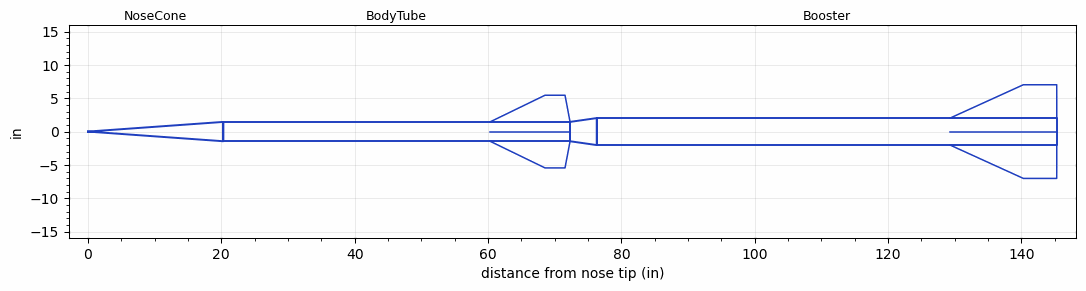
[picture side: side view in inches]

<RASAeroDocument>
 <FileVersion>2</FileVersion>
 <RocketDesign>
  <NoseCone>
   <Length>20.3</Length>
   <Diameter>2.9</Diameter>
   <Shape>Conical</Shape>
   <BluntRadius>0.02</BluntRadius>
   <Location>0</Location>
  </NoseCone>
  <BodyTube>
   <Length>51.9999</Length>
   <Diameter>2.9</Diameter>
   <Location>20.3</Location>
   <Fin>
    <Count>4</Count>
    <Chord>12</Chord>
    <Span>4</Span>
    <SweepDistance>8.2424</SweepDistance>
    <TipChord>3</TipChord>
    <Thickness>0.1875</Thickness>
    <LERadius>0.02</LERadius>
    <Location>12</Location>
    <AirfoilSection>Hexagonal</AirfoilSection>
    <FX1>1</FX1>
    <FX3>1</FX3>
   </Fin>
  </BodyTube>
  <Booster>
   <Length>68.9999</Length>
   <Diameter>4.05</Diameter>
   <InsideDiameter>2.9</InsideDiameter>
   <Location>72.2999</Location>
   <ShoulderLength>4</ShoulderLength>
   <Fin>
    <Count>4</Count>
    <Chord>16</Chord>
    <Span>5</Span>
    <SweepDistance>10.9899</SweepDistance>
    <TipChord>5</TipChord>
    <Thickness>0.25</Thickness>
    <LERadius>0.02</LERadius>
    <Location>16</Location>
    <AirfoilSection>Hexagonal</AirfoilSection>
    <FX1>1</FX1>
    <FX3>1</FX3>
   </Fin>
  </Booster>
  <Surface>Rough Camouflage Paint</Surface>
  <ModifiedBarrowman>False</ModifiedBarrowman>
  <Turbulence>False</Turbulence>
  <UseBooster1>True</UseBooster1>
  <UseBooster2>False</UseBooster2>
 </RocketDesign>
 <LaunchSite>
  <Altitude>0</Altitude>
  <Pressure>29.9214</Pressure>
  <RodAngle>0</RodAngle>
  <RodLength>71.9999</RodLength>
  <Temperature>59</Temperature>
  <WindSpeed>4.4739</WindSpeed>
 </LaunchSite>
 <Recovery>
  <Altitude1>0</Altitude1>
  <Altitude2>0</Altitude2>
  <DeviceType1>None</DeviceType1>
  <DeviceType2>None</DeviceType2>
  <Event1>False</Event1>
  <Event2>False</Event2>
  <Size1>0</Size1>
  <Size2>0</Size2>
  <EventType1>None</EventType1>
  <EventType2>None</EventType2>
  <CD1>0</CD1>
  <CD2>0</CD2>
 </Recovery>
 <SimulationList>
  <Simulation>
   <SustainerEngine>N3650FB  (Polaris)</SustainerEngine>
   <SustainerLaunchWt>20</SustainerLaunchWt>
   <SustainerNozzleDiameter>3</SustainerNozzleDiameter>
   <SustainerCG>47.2</SustainerCG>
   <SustainerIgnitionDelay>7</SustainerIgnitionDelay>
   <Booster1Engine>O6968FB  (Polaris)</Booster1Engine>
   <Booster1LaunchWt>85</Booster1LaunchWt>
   <Booster1SeparationDelay>0</Booster1SeparationDelay>
   <Booster1IgnitionDelay>0</Booster1IgnitionDelay>
   <Booster1CG>93.24</Booster1CG>
   <Booster1NozzleDiameter>4</Booster1NozzleDiameter>
   <IncludeBooster1>True</IncludeBooster1>
   <Booster2Delay>0</Booster2Delay>
   <IncludeBooster2>False</IncludeBooster2>
   <TimetoApogee>251.3539</TimetoApogee>
   <MaxAltitude>944654.2</MaxAltitude>
   <MaxVelocity>9374.686</MaxVelocity>
  </Simulation>
  <Simulation>
   <SustainerLaunchWt>5.4291</SustainerLaunchWt>
   <SustainerCG>47.1957</SustainerCG>
   <SustainerIgnitionDelay>0</SustainerIgnitionDelay>
   <Booster1LaunchWt>15.4542</Booster1LaunchWt>
   <Booster1SeparationDelay>0</Booster1SeparationDelay>
   <Booster1IgnitionDelay>0</Booster1IgnitionDelay>
   <Booster1CG>93.2362</Booster1CG>
   <IncludeBooster1>False</IncludeBooster1>
   <Booster2Delay>0</Booster2Delay>
   <IncludeBooster2>False</IncludeBooster2>
  </Simulation>
 </SimulationList>
</RASAeroDocument>
